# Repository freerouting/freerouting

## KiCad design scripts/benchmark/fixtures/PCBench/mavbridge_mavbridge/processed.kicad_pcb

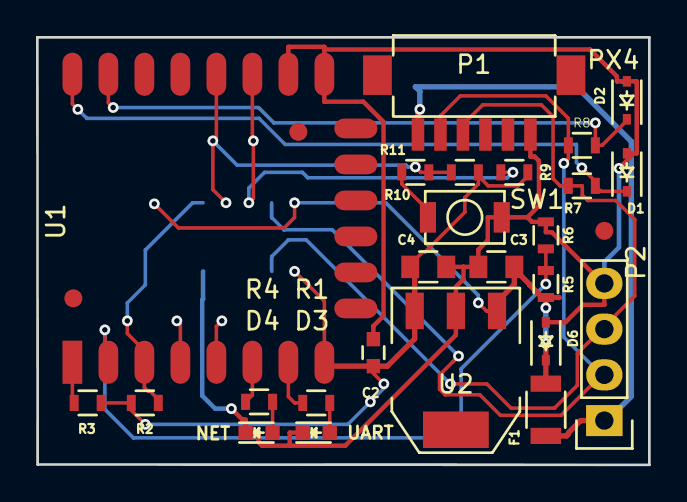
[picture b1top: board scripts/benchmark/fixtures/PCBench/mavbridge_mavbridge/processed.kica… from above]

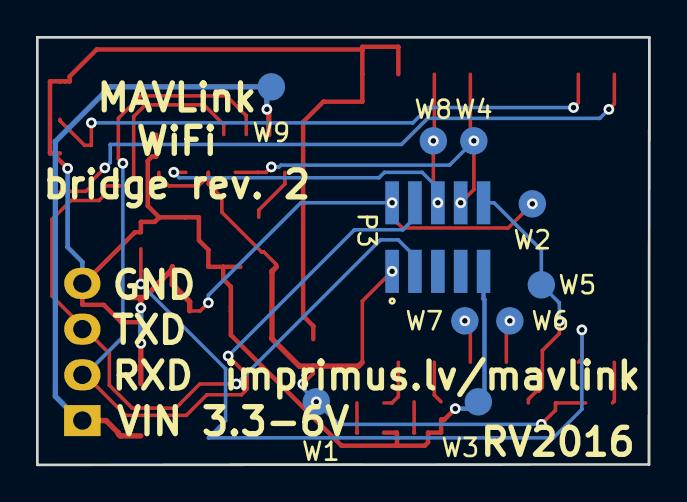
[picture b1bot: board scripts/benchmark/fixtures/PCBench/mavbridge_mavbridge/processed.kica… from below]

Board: 2 copper layers, 34.0 x 23.8 mm, 35 parts (10 on the bottom side), 20 nets.

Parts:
C2: 0.1uF; C_0603
C3, C4: 22uF; C_0805
D1, D2: ZENERsmall; SOD-323
D3: UART; LED-0603
D4: NET; LED-0603
D6: D_Schottky; SOD-323
F1: F_Small; R_1206
P1: PX4; DF13-6
P2: UART; Pin_Header_Straight_1x04
P3: CONN_02X05; Pin_Header_1.27mm_2x5
R1, R4, R7, R8, R11: 120R; R_0603
R2, R3, R5, R6, R9, R10: 10K; R_0603
SW1: SW_PUSH; TACT_SW_TACTD44H20B160
U1: ESP-12E
U2: AP7361; SOT-223
W1, W2, W3, W4, W5, W6, W7, W8, W9: TEST_1P; Measurement_Point_Round-SMD-Pad_Small

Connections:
+3V3: C2.1, C4.1, P3.1, R2.2, R3.2, R9.2, R10.2, U1.8, U2.3, W1.1
+5V: C3.1, D6.1, F1.2, P3.2, R5.2, U2.1, W2.1
/CH_PD: P3.10, R2.1, U1.3, W5.1
/DBG_TX: P3.6, R9.1, U1.17, W8.1
/GPIO0: P3.8, R10.1, R11.2, U1.18, W4.1
/GPIO12: R4.2, U1.6
/GPIO13: R1.2, U1.7
/GPIO14: U1.5, W7.1
/GPIO16: U1.4, W6.1
GND: C2.2, C3.2, C4.2, D1.2, D2.2, D3.1, D4.1, D6.2, P1.6, P2.4, P3.9, R6.1, SW1.2, U1.15, U1.16, U2.2, W3.1
unnamed: D1.1, R7.2, U1.22
unnamed: D2.1, R8.2, U1.21
unnamed: D3.2, R1.1
unnamed: D4.2, R4.1
unnamed: R3.1, U1.1
unnamed: R5.1, R6.2, U1.2
unnamed: R11.1, SW1.1
RXD: P1.2, P2.2, P3.4, R8.1
TXD: P1.3, P2.3, P3.3, R7.1
VPP: F1.1, P1.1, P2.1, W9.1

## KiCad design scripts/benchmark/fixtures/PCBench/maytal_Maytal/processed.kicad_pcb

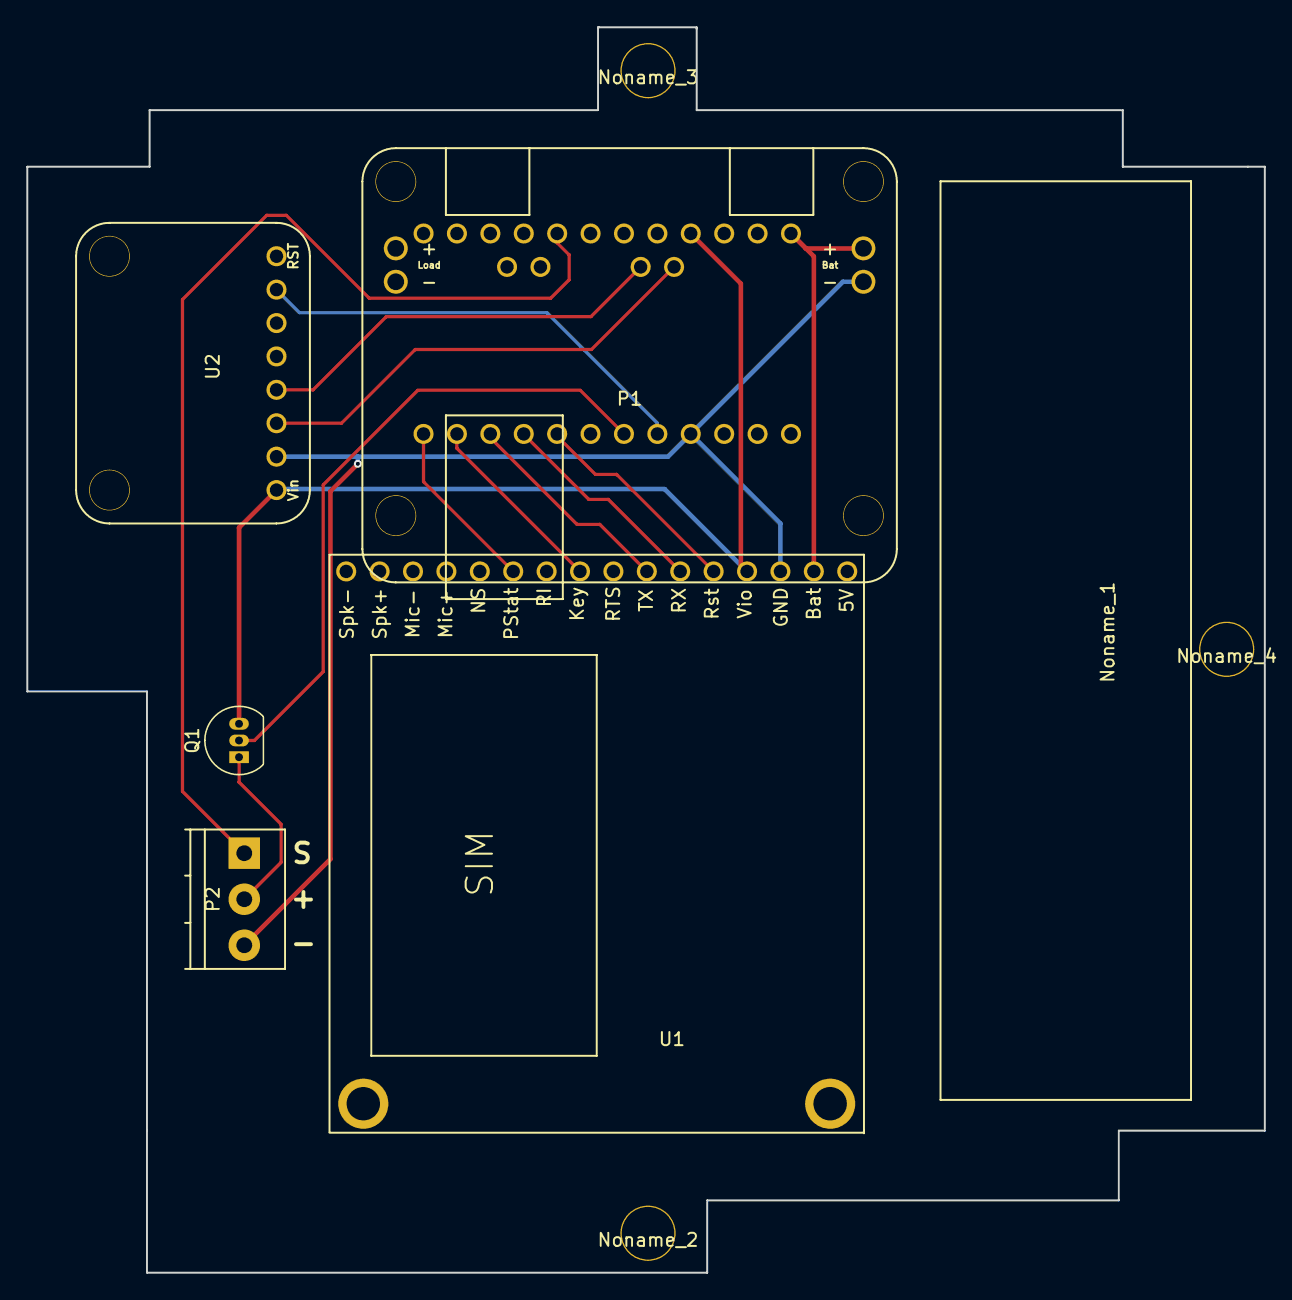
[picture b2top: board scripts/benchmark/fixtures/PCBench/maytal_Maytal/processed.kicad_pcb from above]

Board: 2 copper layers, 94.1 x 94.7 mm, 10 parts (1 on the bottom side), 14 nets.

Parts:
IC1: ArduinoProMini; Arduino_Pro_Mini
Noname_1: LiPo_Cylindrical
Noname_2, Noname_3, Noname_4: M4; M4_Mounting_Hole
P1: LIPO_SOLAR; Adafruit_LiPo_Solar
P2: CONN_01X03; TerminalBlock_Pheonix_PT-3.5mm_3pol
Q1: PN2222A; TO-92_Inline_Narrow_Oval
U1: FONA_808
U2: Adafruit_DS3231

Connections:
BASE: IC1.6, Q1.2
GND: IC1.4, P1.4, P2.3, U1.3, U2.2
unnamed: IC1.5, U2.7
unnamed: IC1.8, U1.5
unnamed: IC1.9, U1.6
unnamed: IC1.10, U1.7
unnamed: IC1.11, U1.9
unnamed: IC1.12, U1.11
unnamed: IC1.17, P2.1
unnamed: P2.2, Q1.1
RAW: IC1.24, P1.3, U1.2
SCL: IC1.26, U2.3
SDA: IC1.25, U2.4
VCC: IC1.21, Q1.3, U1.4, U2.1

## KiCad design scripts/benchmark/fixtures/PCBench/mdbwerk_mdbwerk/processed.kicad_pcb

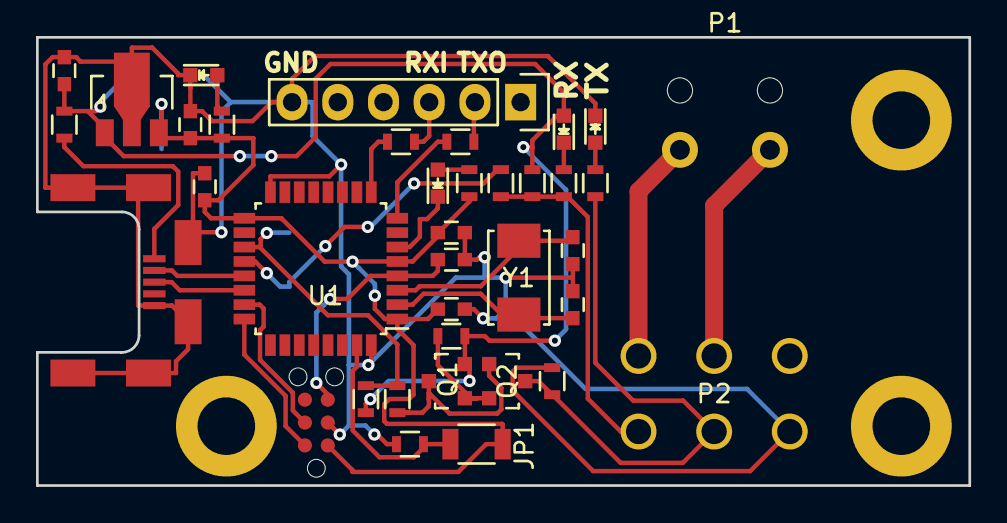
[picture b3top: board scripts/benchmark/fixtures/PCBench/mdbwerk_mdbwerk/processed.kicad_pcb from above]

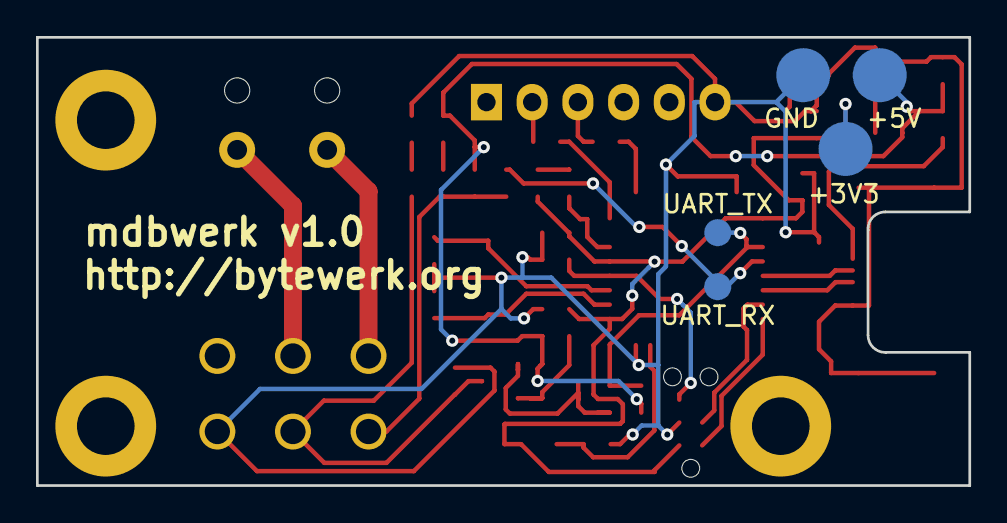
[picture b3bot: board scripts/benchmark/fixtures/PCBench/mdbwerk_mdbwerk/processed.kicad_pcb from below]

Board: 2 copper layers, 51.8 x 24.9 mm, 42 parts (5 on the bottom side), 29 nets.

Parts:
C1, C2, C3, C6: 100nF; C_0603
C4, C5: 18pF; C_0603
C7, C8: 1uF; C_0603
D1, D4: red; LED_0603
D2: yellow; LED_0603
D3: green; LED_0603
JP1: Jumper_NO_Small; R_1206
P1: CONN_01X02; TE-282836-2
P2: CONN_02X03; Molex-39-28-1063
Q1, Q2: MMBT2907; SOT-23
R1, R2, R3, R6, R7, R9, R10: 1K; R_0603
R4, R5: 10K; R_0603
R8: 10R; R_0603
R11: R; R_0603
R12: 0R; R_0603
R13, R14: 100R; R_0603
U1: STM32F042K6Tx; LQFP-32_7x7mm_Pitch0.8mm
U2: MCP1754ST-3302E/MB; SOT89-3_Housing
W1: +5V; Measurement_Point_Round-SMD-Pad_Big
W2: GND; Measurement_Point_Round-SMD-Pad_Big
W3: UART_TX; Measurement_Point_Round-SMD-Pad_Small
W4: UART_RX; Measurement_Point_Round-SMD-Pad_Small
W5: +3V3; Measurement_Point_Round-SMD-Pad_Big
X1: USB; Molex-Micro-USB-B-Middle-Mount
X2: UART; Pin_Header_Straight_1x06
X4: JTAG; TC2030-NL
Y1: 8MHz; ABM3

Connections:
5V_USB: R12.2, X1.1
+3V3: C1.1, C2.1, C3.1, C8.1, JP1.1, R1.1, R2.1, U1.1, U1.5, U1.17, U2.3, W5.1, X4.1
+5V: C7.1, D3.2, Q1.2, R3.1, R6.1, R8.1, R12.1, U2.1, W1.1
+36V: P1.2, P2.1
GND: C1.2, C2.2, C3.2, C4.2, C5.2, C6.2, C7.2, C8.2, D1.1, D4.1, P2.6, R9.2, R11.2, U1.16, U1.32, U2.2, W2.1, X1.5, X1.6, X2.6, X4.3
GNDPWR: P1.1, P2.2
MDB_RXI: P2.4, R5.1, R6.2, R7.2
MDB_TXO: P2.5, Q2.3, R9.1, R10.1
NRST: C6.1, U1.4, X4.5
unnamed: C4.1, U1.2, Y1.1
unnamed: C5.1, U1.3, Y1.2
unnamed: D1.2, R1.2
unnamed: D2.1, U1.6
unnamed: D2.2, R2.2
unnamed: D3.1, R7.1
unnamed: D4.2, R10.2
unnamed: JP1.2, R11.1, U1.31
unnamed: Q1.1, Q2.2, R8.2
unnamed: Q1.3, Q2.1, R4.1
unnamed: R13.1, X2.2
unnamed: R14.1, X2.3
SWCLK: U1.24, X4.2
SWDIO: U1.23, X4.4
USART1_RX: R5.2, U1.20, W4.1
USART1_TX: R3.2, R4.2, U1.19, W3.1
USART2_RX: R14.2, U1.9
USART2_TX: R13.2, U1.8
USB_DM: U1.21, X1.2
USB_DP: U1.22, X1.3
